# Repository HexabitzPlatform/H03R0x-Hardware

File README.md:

# H03R0x-Hardware

Hexabitz 3.3V/2A DC-DC Power Supply Module Hardware Design

Redesign this module using LT3976 + LD39200PU33R. No MCU is required; remove UART ports.

This design must use two hexagons with a 2-layer PCB stack-up.

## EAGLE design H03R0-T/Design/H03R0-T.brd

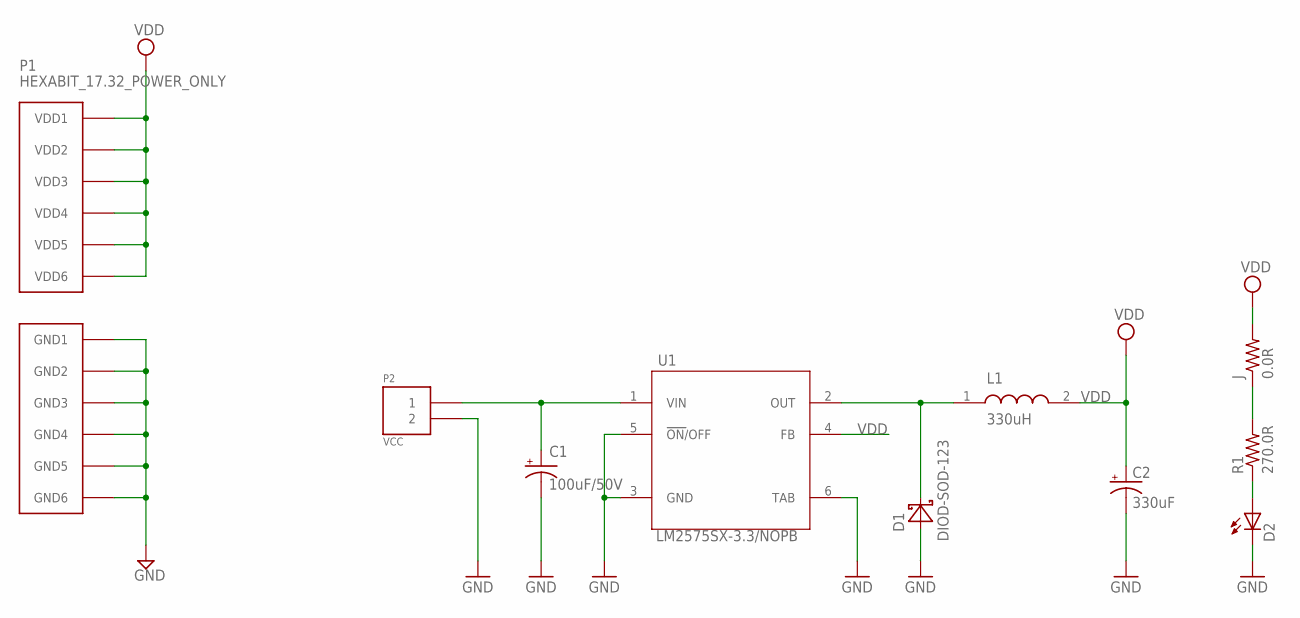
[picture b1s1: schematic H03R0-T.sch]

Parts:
C1: 100uF/50V; E3,5-8; VOLTAGE_RATING_DC 50.0 V; MPN UVR1H101MPD1TD
C2: 330uF; CAPPM7343X200N
D1: DIOD-SOD-123; SOD123; VOLTAGE_RATING_DC 40.0 V; MPN 1N5819HW-7-F
D2: VLMS1300-GS08; MPN VLMTG1300-GS08
J: 0.0R; R-0603; MPN RC0603JR-070RL
L1: 330uH; SRR1280-150M
P1: HEXABIT_17.32_POWER_ONLY
P2: VCC; 1546111-2
R1: 270.0R; R-0603; TOLERANCE ±5%; MPN RC0603FR-07270RL
U1: LM2575SX-3.3/NOPB; TO170P1435X457-6N

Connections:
GND: C1.-, C2.2 (-), D1.1 (A), D2.C, P1.PAD_PD7 (GND1), P1.PAD_PD8 (GND2), P1.PAD_PD9 (GND3), P1.PAD_PD10 (GND4), P1.PAD_PD11 (GND5), P1.PAD_PD12 (GND6), P2.2, U1.3 (GND), U1.5 (ON/OFF), U1.6 (TAB)
unnamed: C1.+, P2.1, U1.1 (VIN)
unnamed: D1.2 (C), L1.1, U1.2 (OUT)
unnamed: D2.A, R1.1
unnamed: J.1, R1.2
VDD: C2.1 (+), J.2, L1.2, P1.PAD_PU7 (VDD1), P1.PAD_PU8 (VDD2), P1.PAD_PU9 (VDD3), P1.PAD_PU10 (VDD4), P1.PAD_PU11 (VDD5), P1.PAD_PU12 (VDD6), U1.4 (FB)

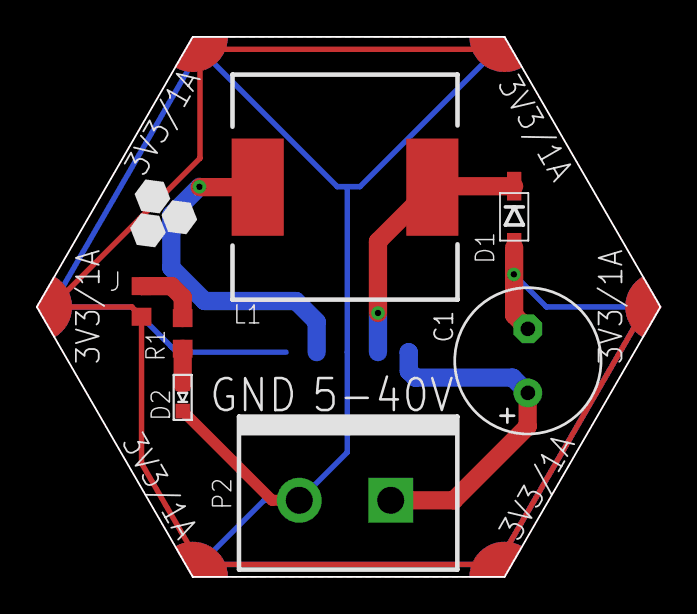
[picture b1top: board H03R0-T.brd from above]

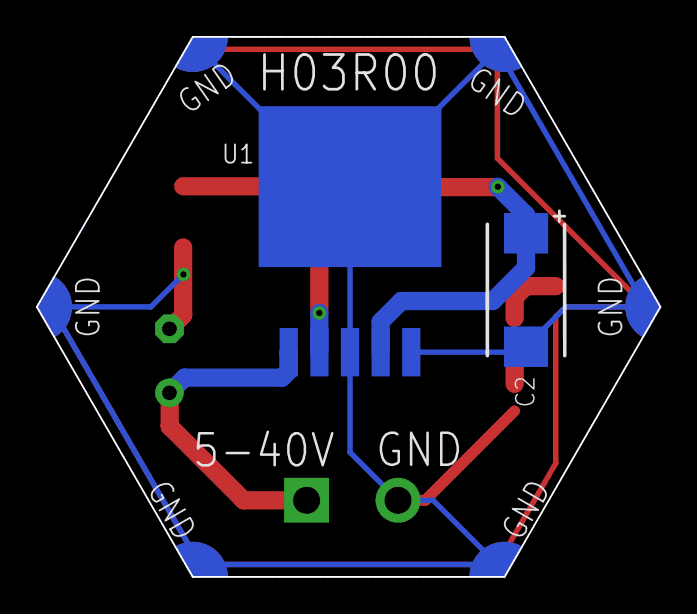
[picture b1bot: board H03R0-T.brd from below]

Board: 2 copper layers, 34.6 x 30.0 mm, 10 parts (2 on the bottom side), 6 nets.

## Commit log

2019-05-23 First release rev 0
2019-05-31 Adding H03R00-J module
    Adding -J module variation using barrel jack power connector
2019-05-31 Update H03R00-T
    Add -T extension to terminal block version
    Update schematics and fix VDD connection
    Regenerate output
2024-01-02 -Standarize the files and folders
2024-01-02 -Fix some missed corrections
2025-10-16 The Altium template has been added.
2025-11-07 Began work on Project.
2025-11-14 Initial Schematic Design
    Completed selection of parts and creation of schematic circuit.
2025-11-14 Schematic Refinement
    Adding Net labels, finalized components for revision 1 of schematic. Cleaned up Schematic. Removed unused backend file.
2025-11-25 Rough placement of all board components
    The schematic now has all components and a rough placement. the only steps left are silkscreen formatting, routing, and final checks.
2025-11-26 Finished rough layout for Module
    Routed, addressed errors, and placed silkscreen components in close to final position.
2025-12-02 H03R0x Manufacturing Files
    Formatted and filled out BOM, created Drill, Gerber, and Pick n Place output files
2025-12-02 Final changes
